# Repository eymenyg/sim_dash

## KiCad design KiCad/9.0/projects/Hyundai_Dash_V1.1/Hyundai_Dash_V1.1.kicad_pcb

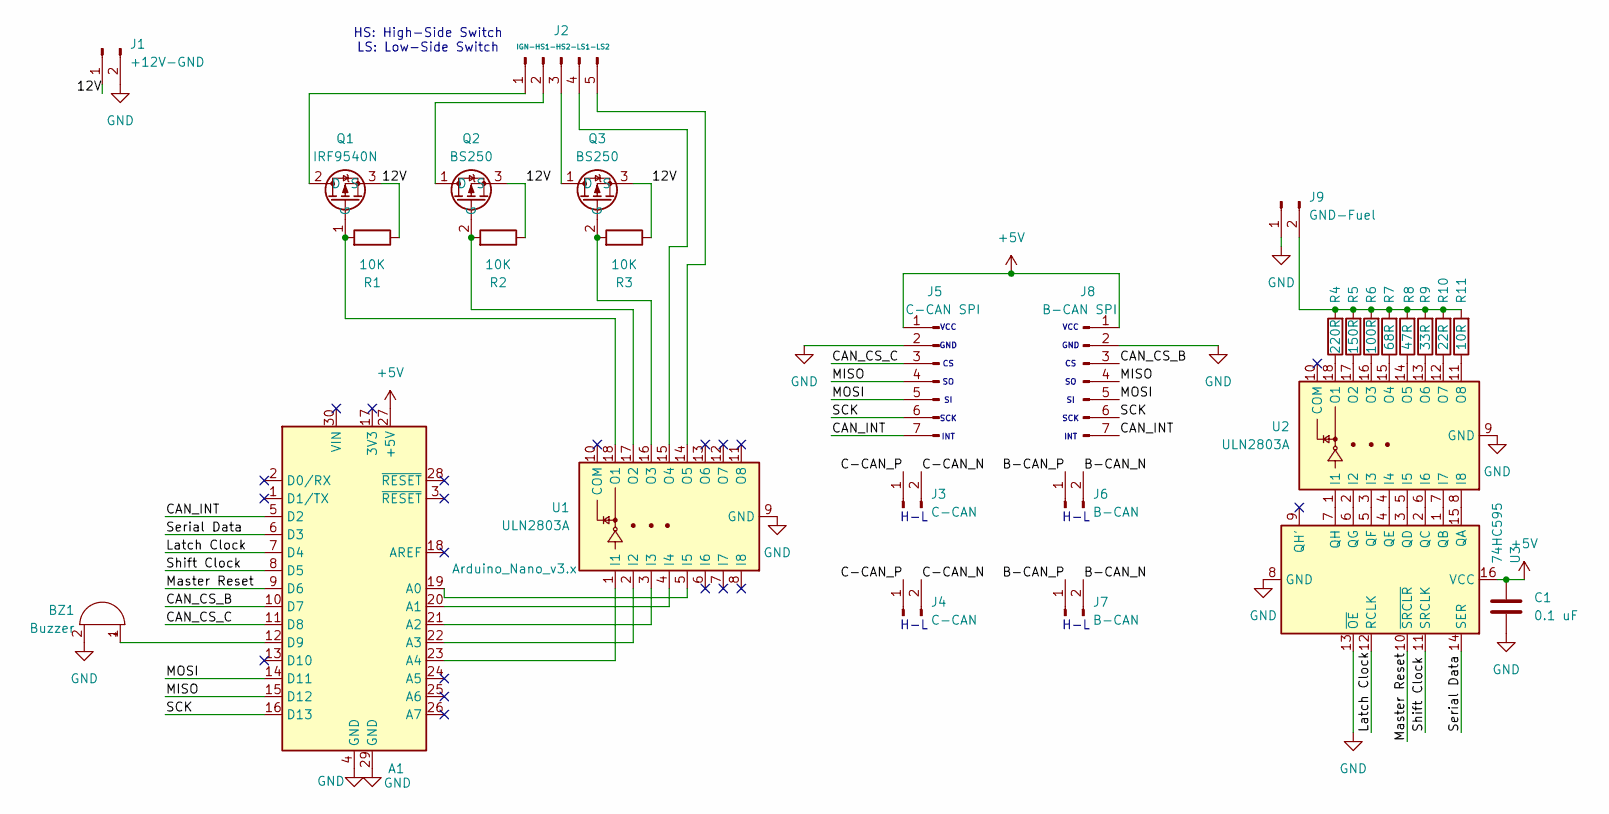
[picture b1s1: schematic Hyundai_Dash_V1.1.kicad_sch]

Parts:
A1: Arduino_Nano_v3.x; Arduino_Nano
BZ1: Buzzer; Buzzer_12x9.5RM7.6
C1: 0.1 uF; C_0603_1608Metric
J1: +12V-GND; JST_XH_B2B-XH-A_1x02_P2.50mm_Vertical
J2: IGN-HS1-HS2-LS1-LS2; JST_XH_B5B-XH-A_1x05_P2.50mm_Vertical
J3: C-CAN; PinSocket_1x02_P2.54mm_Vertical
J4: C-CAN; JST_XH_B2B-XH-A_1x02_P2.50mm_Vertical
J5: C-CAN SPI; PinSocket_1x07_P2.54mm_Vertical
J6: B-CAN; PinSocket_1x02_P2.54mm_Vertical
J7: B-CAN; JST_XH_B2B-XH-A_1x02_P2.50mm_Vertical
J8: B-CAN SPI; PinSocket_1x07_P2.54mm_Vertical
J9: GND-Fuel; JST_XH_B2B-XH-A_1x02_P2.50mm_Vertical
Q1: IRF9540N; TO-220-3_Vertical
Q2, Q3: BS250; TO-92_Inline
R1, R2, R3: 10K; R_0603_1608Metric
R4: 220R; R_2512_6332Metric
R5: 150R; R_2512_6332Metric
R6: 100R; R_2512_6332Metric
R7: 68R; R_2512_6332Metric
R8: 47R; R_2512_6332Metric
R9: 33R; R_2512_6332Metric
R10: 22R; R_2512_6332Metric
R11: 10R; R_2512_6332Metric
U1, U2: ULN2803A; DIP-18_W7.62mm_Socket
U3: 74HC595; DIP-16_W7.62mm_Socket

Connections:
+5V: A1.27 (+5V), C1.1, J5.1, J8.1, U3.16 (VCC)
/12V: J1.1, Q1.3 (S), Q2.3 (S), Q3.3 (S), R1.1, R2.1, R3.1
/B-CAN_N: J6.2, J7.2
/B-CAN_P: J6.1, J7.1
/C-CAN_N: J3.2, J4.2
/C-CAN_P: J3.1, J4.1
/CAN_CS_B: A1.10 (D7), J8.3
/CAN_CS_C: A1.11 (D8), J5.3
/CAN_INT: A1.5 (D2), J5.7, J8.7
/Latch Clock: A1.7 (D4), U3.12 (RCLK)
/MISO: A1.15 (D12), J5.4, J8.4
/MOSI: A1.14 (D11), J5.5, J8.5
/Master Reset: A1.9 (D6), U3.10 (~SRCLR)
/SCK: A1.16 (D13), J5.6, J8.6
/Serial Data: A1.6 (D3), U3.14 (SER)
/Shift Clock: A1.8 (D5), U3.11 (SRCLK)
GND: A1.4 (GND), A1.29 (GND), BZ1.2 (-), C1.2, J1.2, J5.2, J8.2, J9.1, U1.9 (GND), U2.9 (GND), U3.8 (GND), U3.13 (~OE)
unnamed: A1.19 (A0), U1.5 (I5)
unnamed: A1.20 (A1), U1.4 (I4)
unnamed: A1.21 (A2), U1.3 (I3)
unnamed: A1.22 (A3), U1.2 (I2)
unnamed: A1.23 (A4), U1.1 (I1)
unnamed: A1.12 (D9), BZ1.1 (+)
unnamed: J2.1, Q1.2 (D)
unnamed: J2.2, Q2.1 (D)
unnamed: J2.3, Q3.1 (D)
unnamed: J2.4, U1.15 (O4)
unnamed: J2.5, U1.14 (O5)
unnamed: J9.2, R4.2, R5.2, R6.2, R7.2, R8.2, R9.2, R10.2, R11.2
unnamed: Q1.1 (G), R1.2, U1.18 (O1)
unnamed: Q2.2 (G), R2.2, U1.17 (O2)
unnamed: Q3.2 (G), R3.2, U1.16 (O3)
unnamed: U2.1 (I1), U3.7 (QH)
unnamed: U2.2 (I2), U3.6 (QG)
unnamed: U2.3 (I3), U3.5 (QF)
unnamed: U2.4 (I4), U3.4 (QE)
unnamed: U2.5 (I5), U3.3 (QD)
unnamed: U2.6 (I6), U3.2 (QC)
unnamed: U2.7 (I7), U3.1 (QB)
unnamed: U2.8 (I8), U3.15 (QA)
unnamed: R4.1, U2.18 (O1)
unnamed: R5.1, U2.17 (O2)
unnamed: R6.1, U2.16 (O3)
unnamed: R7.1, U2.15 (O4)
unnamed: R8.1, U2.14 (O5)
unnamed: R9.1, U2.13 (O6)
unnamed: R10.1, U2.12 (O7)
unnamed: R11.1, U2.11 (O8)

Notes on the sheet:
HS: High-Side Switch LS: Low-Side Switch
H-L
VCC GND CS SO SI SCK INT

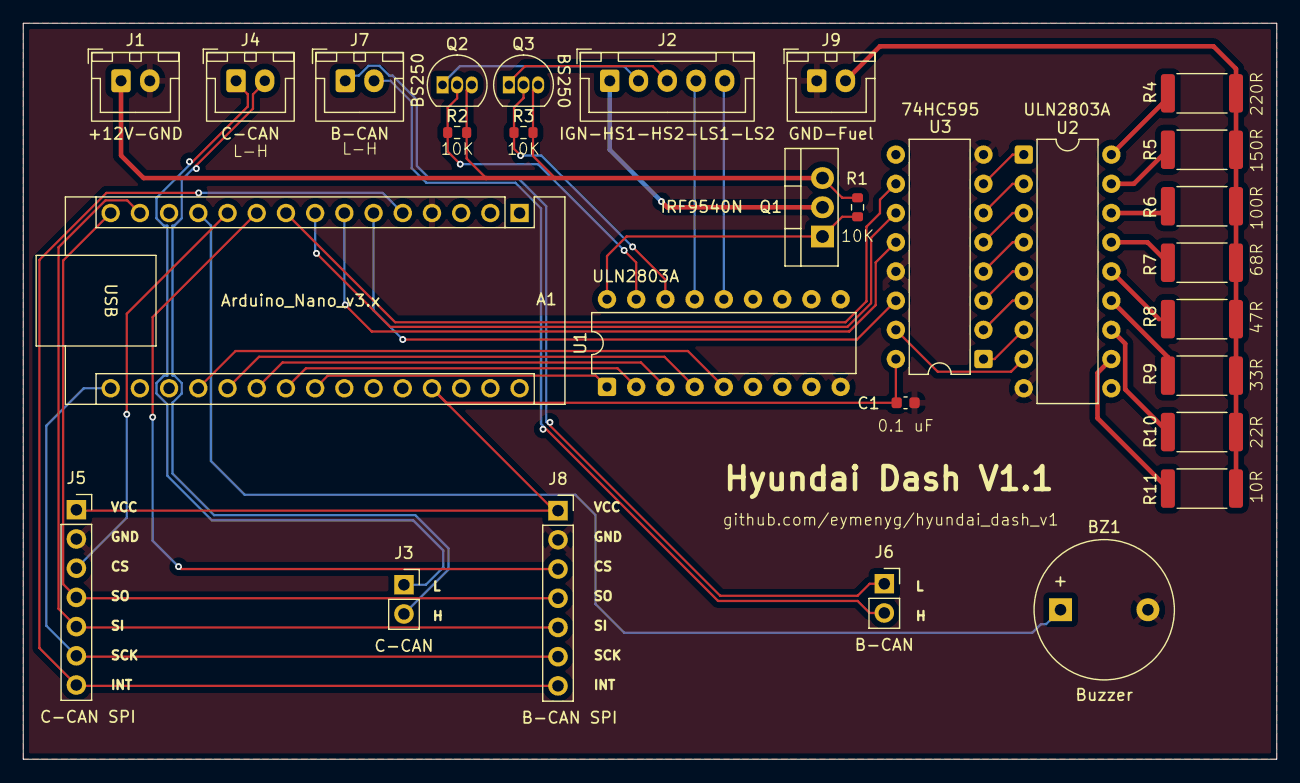
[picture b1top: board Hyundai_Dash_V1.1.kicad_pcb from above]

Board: 2 copper layers, 109.0 x 64.0 mm, 29 parts (0 on the bottom side), 48 nets.

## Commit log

2026-03-01 Optima_TF: set HS2Role to SRS
2026-03-01 Optima_TF: enable turnSignalSound
2026-03-10 disable turn signal sound if light is controlled by CAN and ignition off
2026-03-10 enable turn signal sound for Elantra MD and Sonata YF
2026-03-11 AC: update TC light logic
2026-03-11 Arduino: raise tcIntervalMs to 1000
2026-04-16 KiCad: add Soul_PS_Dash_V1 project based on Hyundai_Dash_V1
2026-04-17 KiCad: update Soul_PS_Dash_V1
2026-04-17 KiCad: create Soul gerbers
2026-04-17 KiCad: Soul backups
2026-04-17 KiCad: Soul.pcb: re-add IC markings on silkscreen
2026-04-22 KiCad: add minor version to project names
2026-04-22 KiCad: bump Hyundai Dash to v1.1
2026-04-22 KiCad: Hyundai_Dash_V1.1: enable pin names of PMOSFETs
2026-04-22 KiCad: Hyundai_Dash_V1.1: remove jumper holder
2026-04-22 KiCad: Hyundai_Dash_V1.1: reassign annotations
2026-04-22 KiCad: Hyundai_Dash_V1.1: update U1-U3 footprints to non-socketed versions
2026-04-22 KiCad: Hyundai_Dash_V1.1: update silkscreen markings
2026-04-22 KiCad: bump Soul PS Dash to v1.1
2026-04-22 KiCad: Hyundai_Dash_V1.1: fix C1 positioning and R4 connection width
2026-04-28 KiCad: Hyundai_Dash_V1.1: fix DRC warnings
2026-04-28 KiCad: Hyundai_Dash_V1.1: J1, J4, J7, J9 set pad hole sizes to .95 mm
2026-04-28 KiCad: Hyundai_Dash_V1.1: gerbers
2026-04-28 ignore KiCad backups
2026-04-28 Arduino: add detailed descriptions for included clusters
2026-05-09 Arduino: update model dir structure and example code
2026-05-09 Arduino: replace '#pragma once' with ifndef block
2026-05-09 Arduino: update library.properties
2026-05-09 Arduino: add needle sweep support
2026-05-13 Arduino: add ECT calibration support, include YF and TF
2026-05-17 Arduino: add ECT calibration support for PS
2026-05-17 Arduino: add ECT calibration support for MD
